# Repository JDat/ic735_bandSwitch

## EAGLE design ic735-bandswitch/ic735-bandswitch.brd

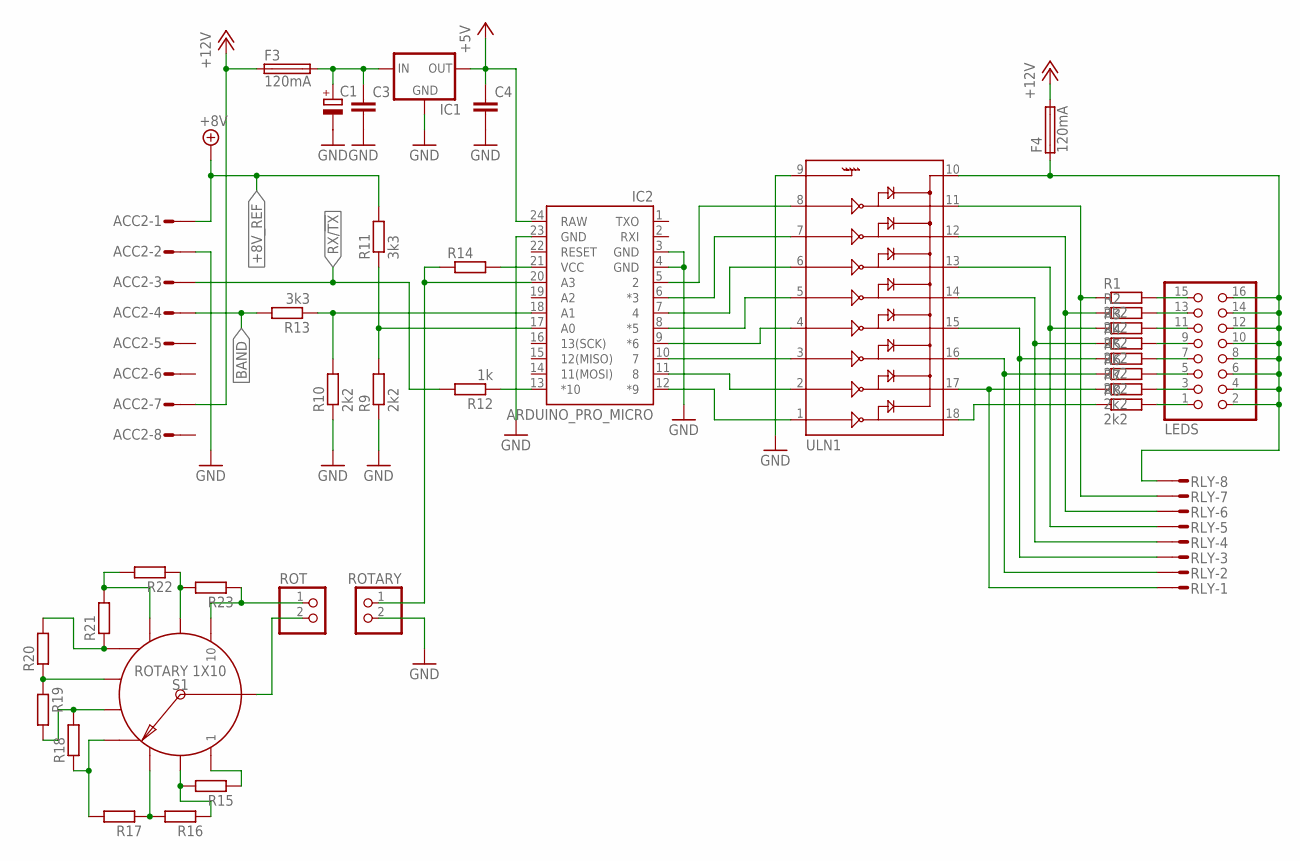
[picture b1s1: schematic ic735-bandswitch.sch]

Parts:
ACC2: S08P
C1: CPOL-EUE2,5-6E; E2,5-6E
C3, C4: C-EU025-024X044; C025-024X044
F3, F4: 120mA; TE5
IC1: 78XXS
IC2: ARDUINO_PRO_MICRO
LEDS: PINHD-2X8; 2X08
R1, R2, R3, R4, R5, R6, R7, R8, R9, R10: 2k2; R0603
R11, R13: 3k3; R0603
R12: 1k; R0603
R14, R15, R16, R17, R18, R19, R20, R21, R22, R23: R-EU_R0603; R0603
RLY: S08P
ROT: PINHD-1X2; 1X02
ROTARY: PINHD-1X2; 1X02
S1: ROTARY 1X10; ROTARY_SWITCH_1X10
ULN1: ULN2803DIP; DIL18

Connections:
+5V: C4.1, IC1.OUT, IC2.24 (RAW)
+8V_REF: ACC2.1, R11.2
+12V: ACC2.7, F3.1, F4.2
BAND: ACC2.4, R13.2
GND: ACC2.2, C1.-, C3.2, C4.2, IC1.GND, IC2.3 (GND), IC2.4 (GND), IC2.23 (GND), R9.1, R10.1, ROTARY.2, ULN1.9
unnamed: IC2.5 (2), ULN1.8
unnamed: IC2.6 (*3), ULN1.7
unnamed: IC2.7 (4), ULN1.6
unnamed: IC2.8 (*5), ULN1.5
unnamed: IC2.9 (*6), ULN1.4
unnamed: IC2.10 (7), ULN1.3
unnamed: IC2.12 (*9), ULN1.1
unnamed: IC2.11 (8), ULN1.2
unnamed: LEDS.15, R1.2
unnamed: LEDS.13, R2.2
unnamed: LEDS.11, R3.2
unnamed: LEDS.9, R4.2
unnamed: LEDS.7, R5.2
unnamed: LEDS.5, R6.2
unnamed: LEDS.3, R7.2
unnamed: LEDS.1, R8.2
unnamed: IC2.18 (A1), R10.2, R13.1
unnamed: R7.1, RLY.1, ULN1.17
unnamed: R6.1, RLY.2, ULN1.16
unnamed: R5.1, RLY.3, ULN1.15
unnamed: R4.1, RLY.4, ULN1.14
unnamed: R3.1, RLY.5, ULN1.13
unnamed: R2.1, RLY.6, ULN1.12
unnamed: R1.1, RLY.7, ULN1.11
unnamed: R8.1, ULN1.18
unnamed: IC2.17 (A0), R9.2, R11.1
unnamed: IC2.13 (*10), R12.1
unnamed: IC2.20 (A3), R14.1, ROTARY.1
unnamed: IC2.21 (VCC), R14.2
unnamed: C1.+, C3.1, F3.2, IC1.IN
unnamed: F4.1, LEDS.2, LEDS.4, LEDS.6, LEDS.8, LEDS.10, LEDS.12, LEDS.14, LEDS.16, RLY.8, ULN1.10
unnamed: R15.1, S1.1
unnamed: R15.2, R16.1, S1.2
unnamed: R23.1, ROT.1, S1.10
unnamed: R16.2, R17.1, S1.3
unnamed: R19.1, R20.1, S1.6
unnamed: R17.2, R18.1, S1.4
unnamed: R18.2, R19.2, S1.5
unnamed: ROT.2, S1.COMMON
unnamed: R20.2, R21.1, S1.7
unnamed: R21.2, R22.2, S1.8
unnamed: R22.1, R23.2, S1.9
RX/!TX: ACC2.3, R12.2

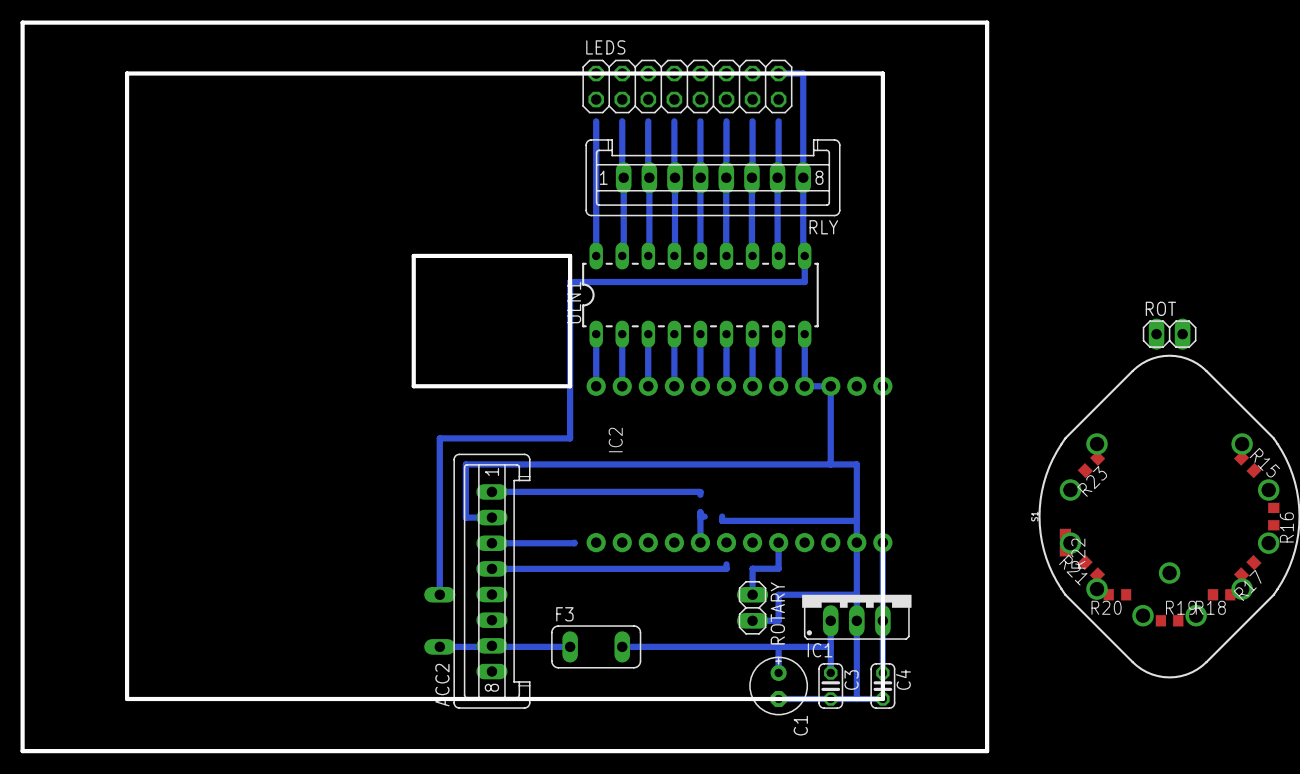
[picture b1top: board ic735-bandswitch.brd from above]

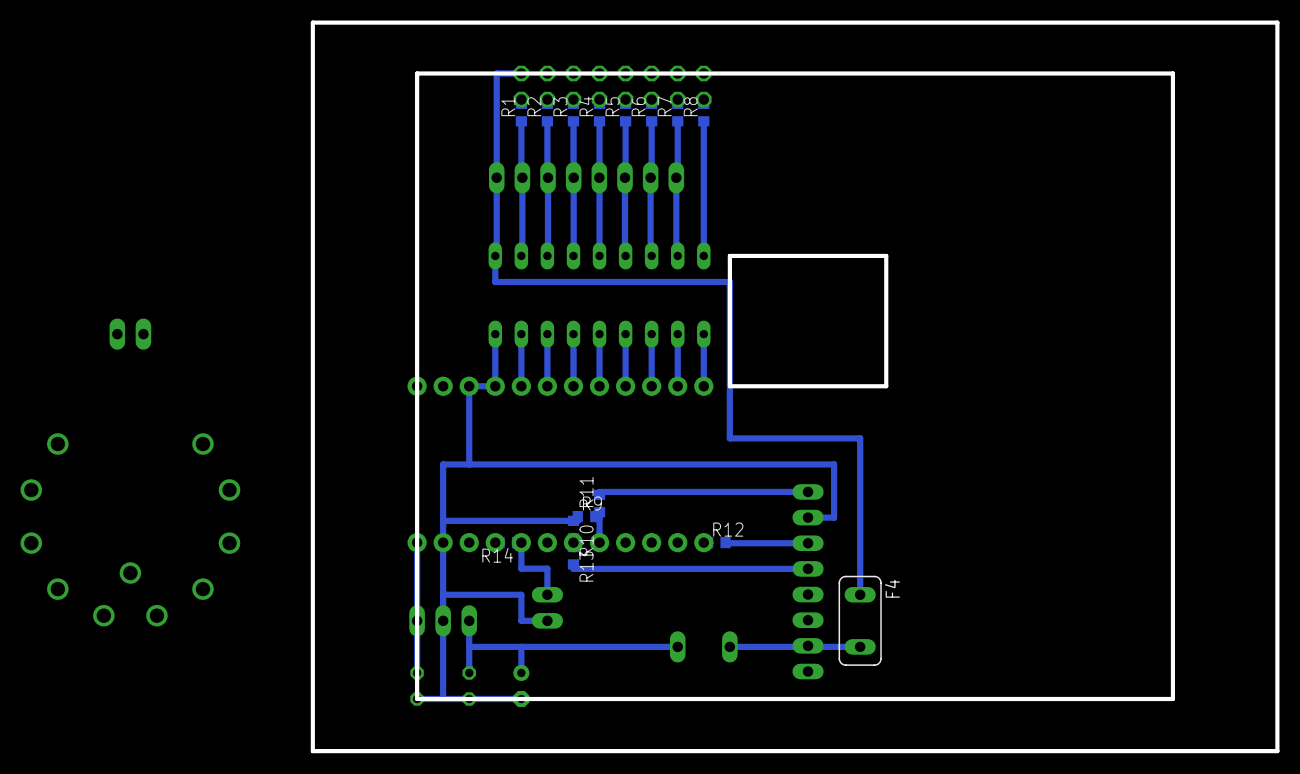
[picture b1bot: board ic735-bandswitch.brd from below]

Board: 2 copper layers, 94.0 x 71.0 mm, 37 parts (15 on the bottom side), 48 nets.

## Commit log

2020-10-29 Update ic735_bandSwitch.ino
    Small typo fixes and comments
2021-06-14 Add rotary switch and pdf
    Add rotary switch for better understanding.
    Add PDF files.
2021-06-14 Minor fixes
    Some minor and syntax fixes. Not tested yet.

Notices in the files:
parts and their libraries:
SparkFun-Boards: Licensing: Creative Commons ShareAlike 4.0 International - https://creativecommons.org/licenses/by-sa/4.0
